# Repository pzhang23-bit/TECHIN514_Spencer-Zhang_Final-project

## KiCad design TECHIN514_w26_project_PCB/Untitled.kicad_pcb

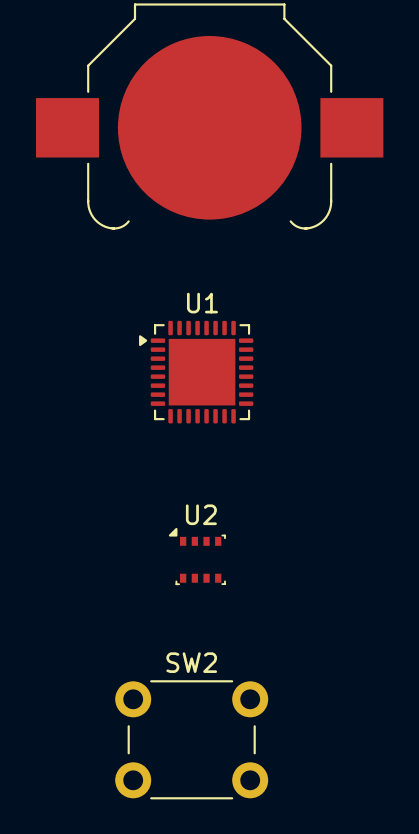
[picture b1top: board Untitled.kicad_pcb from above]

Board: 2 copper layers, 4 parts (0 on the bottom side), 5 nets, no tracks yet.

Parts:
BT1: Battery; BatteryHolder_Keystone_3000_1x12mm
SW2: SW_Push; SW_PUSH_6mm
U1: ESP32-C3; QFN-32-1EP_5x5mm_P0.5mm_EP3.7x3.7mm
U2: BME280; Bosch_LGA-8_2.5x2.5mm_P0.65mm_ClockwisePinNumbering

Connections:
/unconnected-(BT1-+-Pad1): BT1.1 (+), U1.2 (VDD3P3), U1.3 (VDD3P3), U1.14 (GPIO8), U2.2 (CSB), U2.3 (SDI), U2.8 (VDD)
unnamed: BT1.2 (-), SW2.2, U1.33 (GND), U2.1 (GND), U2.5 (SDO), U2.7 (GND)
unnamed: SW2.1, U1.6 (GPIO2)
unnamed: U1.15 (GPIO9), U2.4 (SCK)
unnamed: U1.31 (VDDA), U1.32 (VDDA)

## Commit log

2026-01-30 Create TECHIN514_PCBdesign
2026-01-30 Create TECHIN514_w26_project_PCB
2026-01-30 Update TECHIN514_w26_project_PCB
2026-03-02 Create Second device
